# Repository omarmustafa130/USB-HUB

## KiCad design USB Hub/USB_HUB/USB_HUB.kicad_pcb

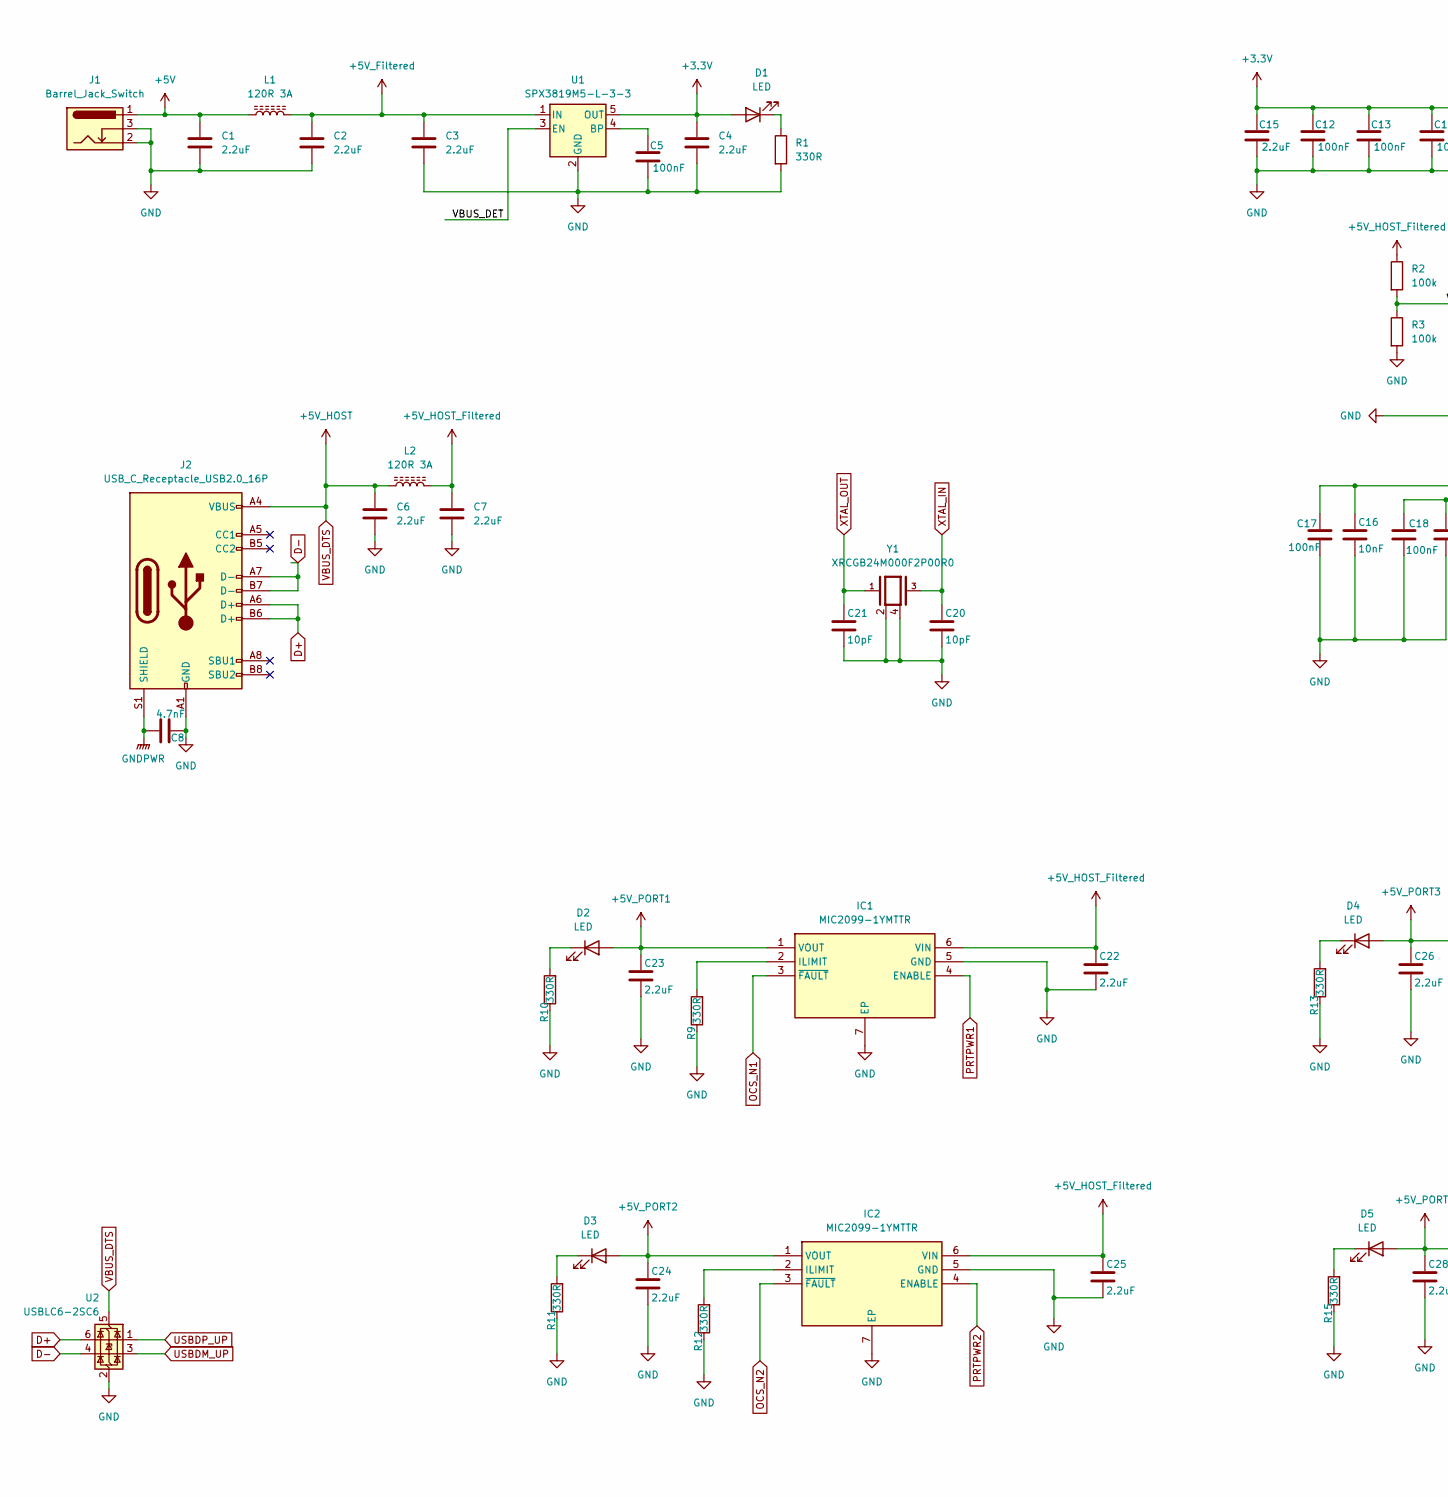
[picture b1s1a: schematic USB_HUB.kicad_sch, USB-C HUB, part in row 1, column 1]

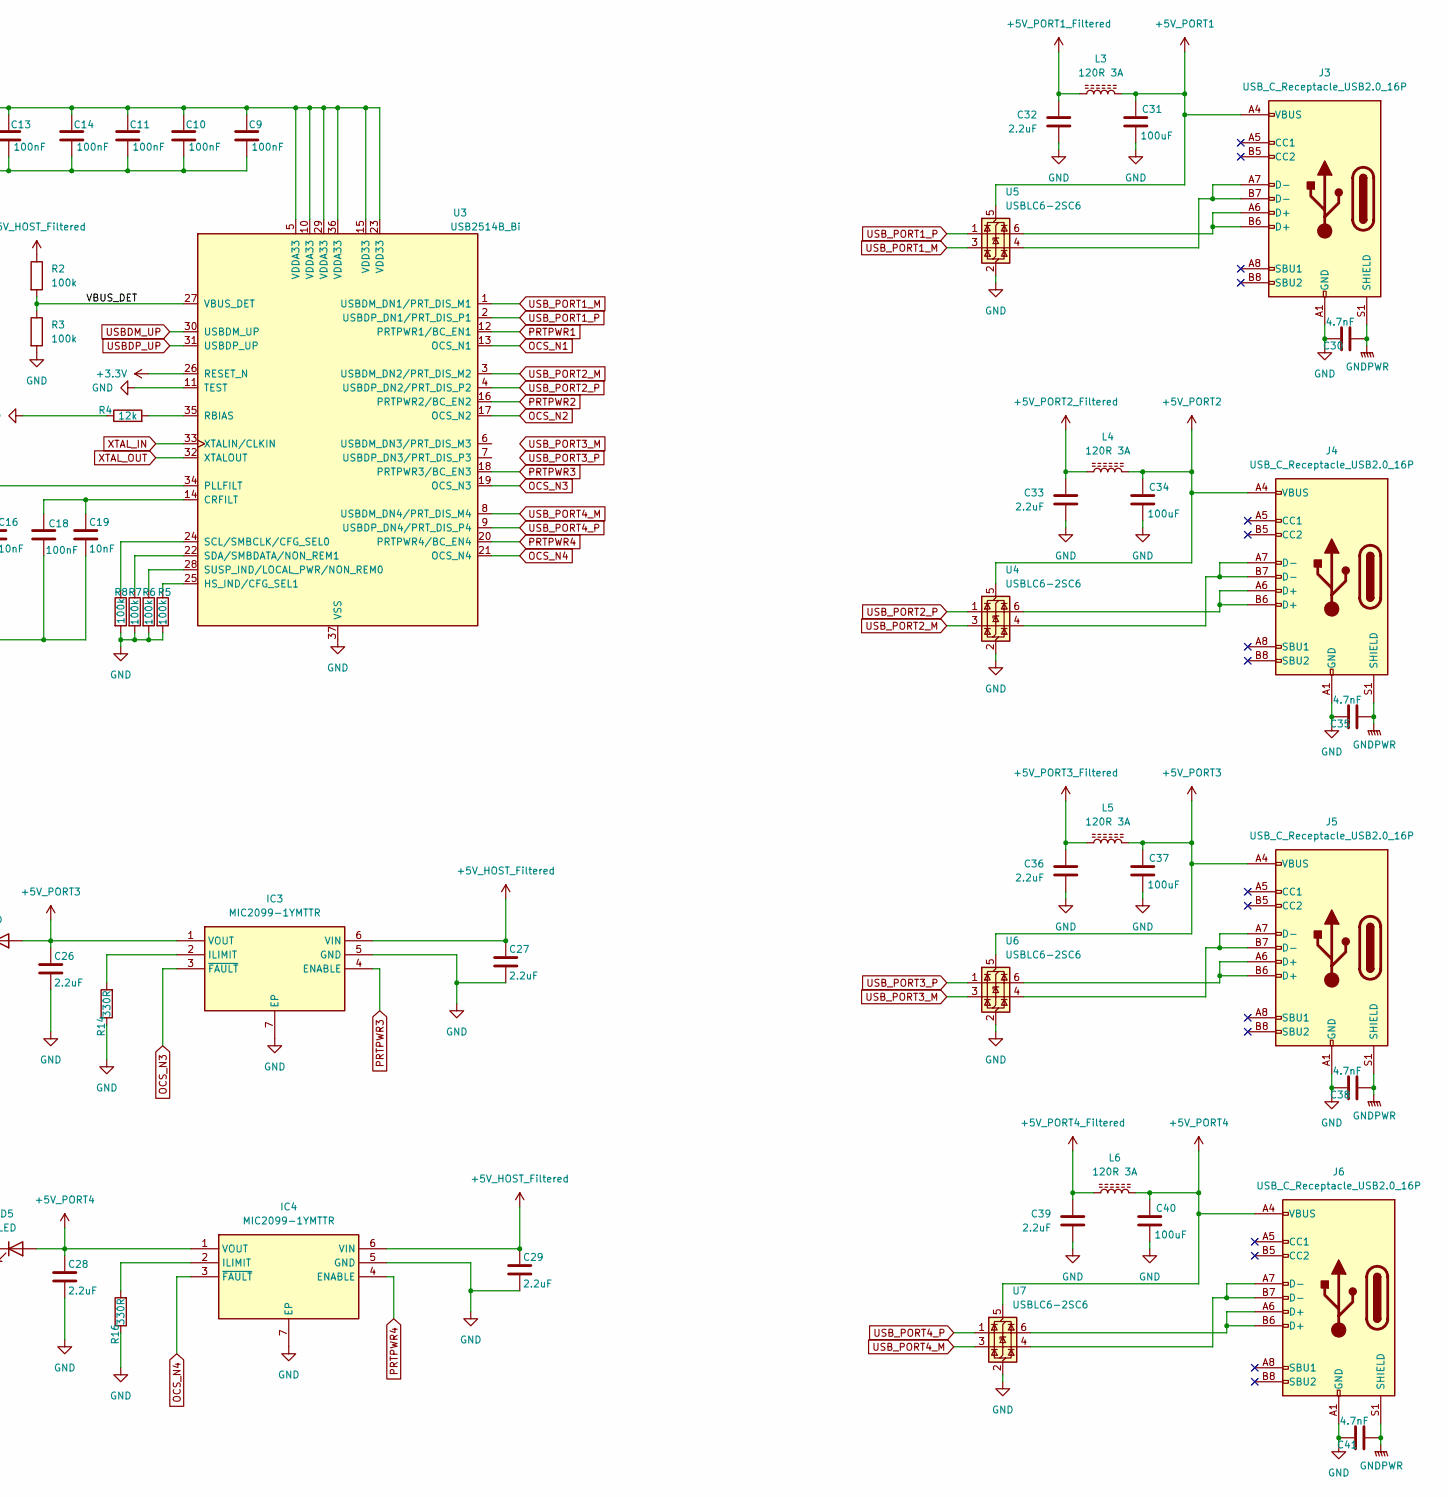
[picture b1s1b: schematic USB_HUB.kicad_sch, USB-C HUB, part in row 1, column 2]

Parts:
C1, C2, C3, C4, C6, C7, C15, C22, C23, C24, C25, C26, C27, C28, C29, C32, C33, C36, C39: 2.2uF; C_0603_1608Metric
C5, C9, C10, C11, C12, C13, C14, C17, C18: 100nF; C_0603_1608Metric
C8, C30, C35, C38, C41: 4.7nF; C_0603_1608Metric
C16, C19: 10nF; C_0603_1608Metric
C20, C21: 10pF; C_0603_1608Metric
C31, C34, C37, C40: 100uF; C_0603_1608Metric
D1, D2, D3, D4, D5: LED; LED_0603_1608Metric
IC1, IC2, IC3, IC4: MIC2099-1YMTTR; MIC2099_SON50P160X160X60-7N-D; Manufacturer_Part_Number MIC2099-1YMTTR
J1: Barrel_Jack_Switch; 694106301002_1
J2, J3, J4, J5, J6: USB_C_Receptacle_USB2.0_16P; USB_C_Receptacle_HRO_TYPE-C-31-M-12
L1, L2, L3, L4, L5, L6: 120R 3A; L_0603_1608Metric
R1, R9, R10, R11, R12, R13, R14, R15, R16: 330R; R_0603_1608Metric
R2, R3, R5, R6, R7, R8: 100k; R_0603_1608Metric
R4: 12k; R_0603_1608Metric
U1: SPX3819M5-L-3-3; SOT-23-5
U2, U4, U5, U6, U7: USBLC6-2SC6; SOT-23-6
U3: USB2514B_Bi; QFN-36-1EP_6x6mm_P0.5mm_EP3.7x3.7mm
Y1: XRCGB24M000F2P00R0; OSC_XRCGB24M000F2P00R0; PARTREV N/A

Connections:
+3.3V: C4.1, C9.1, C10.1, C11.1, C12.1, C13.1, C14.1, C15.1, D1.2 (A), U1.5 (OUT), U3.5 (VDDA33), U3.10 (VDDA33), U3.15 (VDD33), U3.23 (VDD33), U3.26 (RESET_N), U3.29 (VDDA33), U3.36 (VDDA33)
+5V: C1.1, J1.1, L1.1
+5V_Filtered: C2.1, C3.1, L1.2, U1.1 (IN)
+5V_HOST_Filtered: C7.1, C22.1, C25.1, C27.1, C29.1, IC1.6 (VIN), IC2.6 (VIN), IC3.6 (VIN), IC4.6 (VIN), L2.2, R2.1
+5V_PORT1: C23.1, C31.1, D2.2 (A), IC1.1 (VOUT), J3.A4 (VBUS), J3.A9 (VBUS), J3.B4 (VBUS), J3.B9 (VBUS), L3.1, U5.5 (VBUS)
+5V_PORT1_Filtered: C32.1, L3.2
+5V_PORT2: C24.1, C34.1, D3.2 (A), IC2.1 (VOUT), J4.A4 (VBUS), J4.A9 (VBUS), J4.B4 (VBUS), J4.B9 (VBUS), L4.1, U4.5 (VBUS)
+5V_PORT2_Filtered: C33.1, L4.2
+5V_PORT3: C26.1, C37.1, D4.2 (A), IC3.1 (VOUT), J5.A4 (VBUS), J5.A9 (VBUS), J5.B4 (VBUS), J5.B9 (VBUS), L5.1, U6.5 (VBUS)
+5V_PORT3_Filtered: C36.1, L5.2
+5V_PORT4: C28.1, C40.1, D5.2 (A), IC4.1 (VOUT), J6.A4 (VBUS), J6.A9 (VBUS), J6.B4 (VBUS), J6.B9 (VBUS), L6.1, U7.5 (VBUS)
+5V_PORT4_Filtered: C39.1, L6.2
/VBUS_DET: R2.2, R3.1, U1.3 (EN), U3.27 (VBUS_DET)
D+: J2.A6 (D+), J2.B6 (D+), U2.6 (I/O1)
D-: J2.A7 (D-), J2.B7 (D-), U2.4 (I/O2)
GND: C1.2, C2.2, C3.2, C4.2, C5.2, C6.2, C7.2, C8.2, C9.2, C10.2, C11.2, C12.2, C13.2, C14.2, C15.2, C16.2, C17.2, C18.2, C19.2, C20.2, C21.2, C22.2, C23.2, C24.2, C25.2, C26.2, C27.2, C28.2, C29.2, C30.2, C31.2, C32.2, C33.2, C34.2, C35.2, C36.2, C37.2, C38.2, C39.2, C40.2, C41.2, IC1.5 (GND), IC1.7 (EP), IC2.5 (GND), IC2.7 (EP), IC3.5 (GND), IC3.7 (EP), IC4.5 (GND), IC4.7 (EP), J1.2, J1.3, J2.A1 (GND), J2.A12 (GND), J2.B1 (GND), J2.B12 (GND), J3.A1 (GND), J3.A12 (GND), J3.B1 (GND), J3.B12 (GND), J4.A1 (GND), J4.A12 (GND), J4.B1 (GND), J4.B12 (GND), J5.A1 (GND), J5.A12 (GND), J5.B1 (GND), J5.B12 (GND), J6.A1 (GND), J6.A12 (GND), J6.B1 (GND), J6.B12 (GND), R1.2, R3.2, R4.1, R5.2, R6.2, R7.2, R8.2, R9.1, R10.1, R11.1, R12.1, R13.1, R14.1, R15.1, R16.1, U1.2 (GND), U2.2 (GND), U3.11 (TEST), U3.37 (VSS), U4.2 (GND), U5.2 (GND), U6.2 (GND), U7.2 (GND), Y1.2, Y1.4
GNDPWR: C8.1, C30.1, C35.1, C38.1, C41.1, J2.S1 (SHIELD), J3.S1 (SHIELD), J4.S1 (SHIELD), J5.S1 (SHIELD), J6.S1 (SHIELD)
unnamed: D1.1 (K), R1.1
unnamed: D2.1 (K), R10.2
unnamed: D3.1 (K), R11.2
unnamed: D4.1 (K), R13.2
unnamed: D5.1 (K), R15.2
unnamed: IC1.2 (ILIMIT), R9.2
unnamed: IC2.2 (ILIMIT), R12.2
unnamed: IC3.2 (ILIMIT), R14.2
unnamed: IC4.2 (ILIMIT), R16.2
unnamed: J3.A6 (D+), J3.B6 (D+), U5.6 (I/O1)
unnamed: J3.A7 (D-), J3.B7 (D-), U5.4 (I/O2)
unnamed: J4.A6 (D+), J4.B6 (D+), U4.6 (I/O1)
unnamed: J4.A7 (D-), J4.B7 (D-), U4.4 (I/O2)
unnamed: J5.A6 (D+), J5.B6 (D+), U6.6 (I/O1)
unnamed: J5.A7 (D-), J5.B7 (D-), U6.4 (I/O2)
unnamed: J6.A6 (D+), J6.B6 (D+), U7.6 (I/O1)
unnamed: J6.A7 (D-), J6.B7 (D-), U7.4 (I/O2)
unnamed: C5.1, U1.4 (BP)
unnamed: C18.1, C19.1, U3.14 (CRFILT)
unnamed: R5.1, U3.25 (HS_IND/CFG_SEL1)
unnamed: C16.1, C17.1, U3.34 (PLLFILT)
unnamed: R4.2, U3.35 (RBIAS)
unnamed: R8.1, U3.24 (SCL/SMBCLK/CFG_SEL0)
unnamed: R7.1, U3.22 (SDA/SMBDATA/NON_REM1)
unnamed: R6.1, U3.28 (SUSP_IND/LOCAL_PWR/NON_REM0)
OCS_N1: IC1.3 (~FAULT), U3.13 (OCS_N1)
OCS_N2: IC2.3 (~FAULT), U3.17 (OCS_N2)
OCS_N3: IC3.3 (~FAULT), U3.19 (OCS_N3)
OCS_N4: IC4.3 (~FAULT), U3.21 (OCS_N4)
PRTPWR1: IC1.4 (ENABLE), U3.12 (PRTPWR1/BC_EN1)
PRTPWR2: IC2.4 (ENABLE), U3.16 (PRTPWR2/BC_EN2)
PRTPWR3: IC3.4 (ENABLE), U3.18 (PRTPWR3/BC_EN3)
PRTPWR4: IC4.4 (ENABLE), U3.20 (PRTPWR4/BC_EN4)
USBDM_UP: U2.3 (I/O2), U3.30 (USBDM_UP)
USBDP_UP: U2.1 (I/O1), U3.31 (USBDP_UP)
USB_PORT1_M: U3.1 (USBDM_DN1/PRT_DIS_M1), U5.3 (I/O2)
USB_PORT1_P: U3.2 (USBDP_DN1/PRT_DIS_P1), U5.1 (I/O1)
USB_PORT2_M: U3.3 (USBDM_DN2/PRT_DIS_M2), U4.3 (I/O2)
USB_PORT2_P: U3.4 (USBDP_DN2/PRT_DIS_P2), U4.1 (I/O1)
USB_PORT3_M: U6.3 (I/O2)
USB_PORT3_P: U6.1 (I/O1)
USB_PORT4_M: U3.8 (USBDM_DN4/PRT_DIS_M4), U7.3 (I/O2)
USB_PORT4_P: U3.9 (USBDP_DN4/PRT_DIS_P4), U7.1 (I/O1)
VBUS_DTS: C6.1, J2.A4 (VBUS), J2.A9 (VBUS), J2.B4 (VBUS), J2.B9 (VBUS), L2.1, U2.5 (VBUS)
XTAL_IN: C20.1, U3.33 (XTALIN/CLKIN), Y1.3
XTAL_OUT: C21.1, U3.32 (XTALOUT), Y1.1

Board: 2 copper layers, 86 parts (0 on the bottom side), 61 nets, no tracks yet.

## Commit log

2025-05-22 Schematics done
